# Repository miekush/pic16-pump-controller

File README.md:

# pic16-pump-controller
PIC16 based Pump Controller for Smart Plant Watering and Coffee Makers

# PCB

# License

MKE supports the open source hardware community by sharing hardware design files freely on GitHub!

Please support MKE by purchasing products on [Tindie](https://www.tindie.com/stores/mkengineering/)!

Designed by Mike Kushnerik (miekush)

Licensed under [Creative Commons Attribution-ShareAlike CC BY-SA 4.0](http://creativecommons.org/licenses/by-sa/4.0/)

All text above must be included in any redistribution!

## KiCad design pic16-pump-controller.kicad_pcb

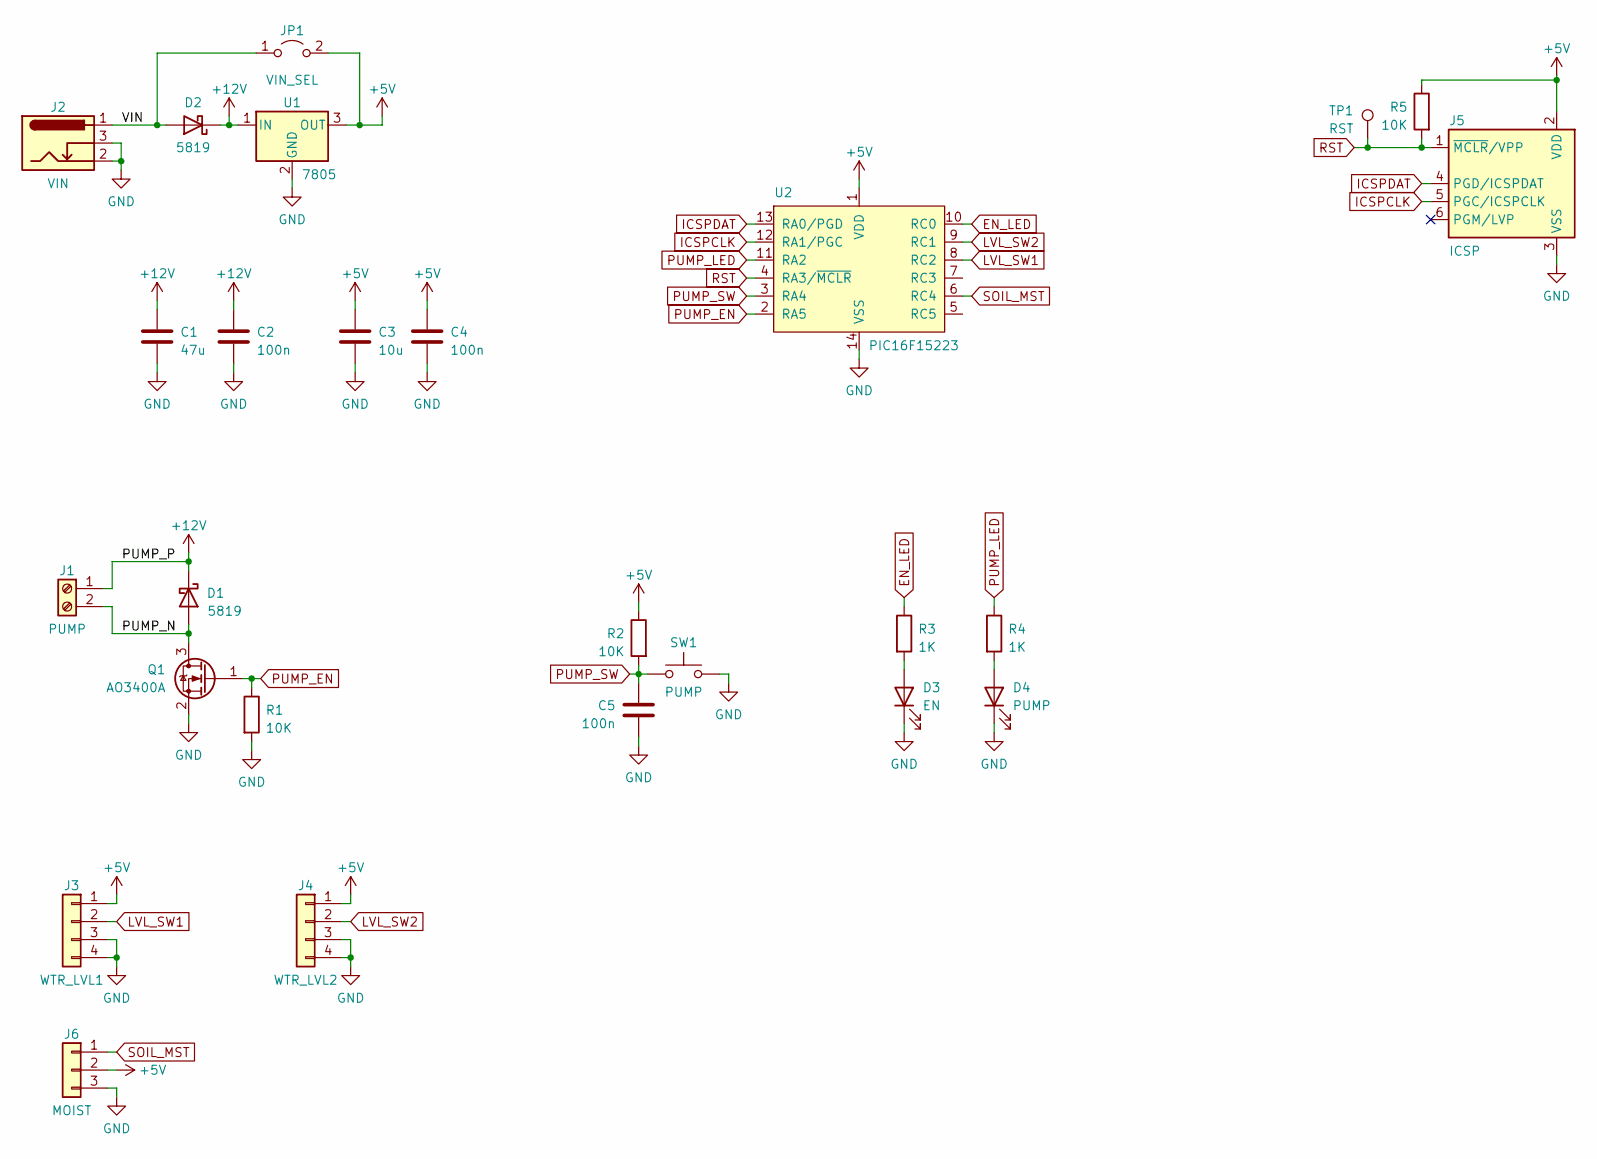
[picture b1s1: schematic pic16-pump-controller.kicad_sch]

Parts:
C1: 47u; CP_Elec_6.3x5.8
C2, C4, C5: 100n; C_0603_1608Metric
C3: 10u; C_0805_2012Metric
D1, D2: 5819; D_SMA
D3: EN; LED_0603_1608Metric
D4: PUMP; LED_0603_1608Metric
J1: PUMP; TerminalBlock_bornier-2_P5.08mm
J2: VIN; BarrelJack_GCT_DCJ200-10-A_Horizontal
J3: WTR_LVL1; PinHeader_1x04_P2.54mm_Vertical
J4: WTR_LVL2; PinHeader_1x04_P2.54mm_Vertical
J5: ICSP; Tag-Connect_TC2030-IDC-NL_2x03_P1.27mm_Vertical
J6: MOIST; PinHeader_1x03_P2.54mm_Vertical
JP1: VIN_SEL; PinHeader_1x02_P2.54mm_Vertical
Q1: AO3400A; SOT-23
R1, R2, R5: 10K; R_0603_1608Metric
R3, R4: 1K; R_0603_1608Metric
SW1: PUMP; SW_Push_1P1T_NO_6x6mm_H9.5mm
TP1: RST; PinHeader_1x01_P2.54mm_Vertical
U1: 7805; SOT-223-3_TabPin2
U2: PIC16F15223; SOIC-14_3.9x8.7mm_P1.27mm

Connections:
+5V: C3.1, C4.1, J3.1, J4.1, J5.2 (VDD), J6.2, JP1.2 (B), R2.1, R5.1, U1.3 (OUT), U2.1 (VDD)
+12V: C1.1, C2.1, D1.1 (K), D2.1 (K), J1.1, U1.1 (IN)
/PUMP_N: D1.2 (A), J1.2, Q1.3 (D)
/VIN: D2.2 (A), J2.1, JP1.1 (A)
EN_LED: R3.1, U2.10 (RC0)
GND: C1.2, C2.2, C3.2, C4.2, C5.2, D3.1 (K), D4.1 (K), J2.2, J2.3, J3.3, J3.4, J4.3, J4.4, J5.3 (VSS), J6.3, Q1.2 (S), R1.2, SW1.2, U1.2 (GND), U2.14 (VSS)
ICSPCLK: J5.5 (PGC/ICSPCLK), U2.12 (RA1/PGC)
ICSPDAT: J5.4 (PGD/ICSPDAT), U2.13 (RA0/PGD)
LVL_SW1: J3.2, U2.8 (RC2)
LVL_SW2: J4.2, U2.9 (RC1)
unnamed: D3.2 (A), R3.2
unnamed: D4.2 (A), R4.2
PUMP_EN: Q1.1 (G), R1.1, U2.2 (RA5)
PUMP_LED: R4.1, U2.11 (RA2)
PUMP_SW: C5.1, R2.2, SW1.1, U2.3 (RA4)
RST: J5.1 (~MCLR/VPP), R5.2, TP1.1, U2.4 (RA3/~MCLR)
SOIL_MST: J6.1, U2.6 (RC4)

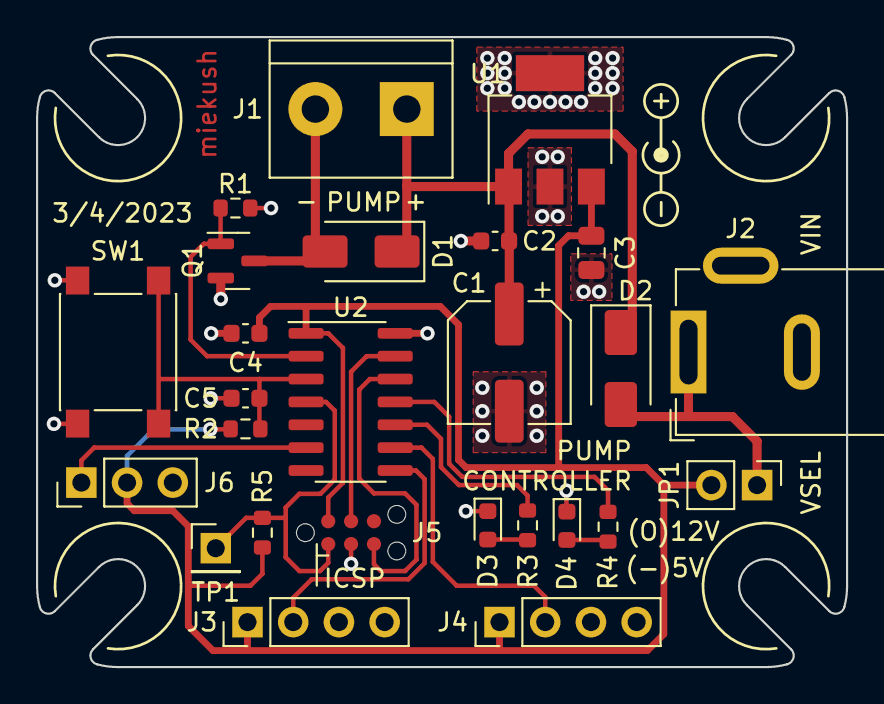
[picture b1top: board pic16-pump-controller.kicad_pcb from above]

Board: 2 copper layers, 45.0 x 35.0 mm, 26 parts (0 on the bottom side), 17 nets.

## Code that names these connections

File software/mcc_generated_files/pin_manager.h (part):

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// get/set PUMP_LED aliases
#define PUMP_LED_TRIS                 TRISAbits.TRISA2
#define PUMP_LED_LAT                  LATAbits.LATA2
#define PUMP_LED_PORT                 PORTAbits.RA2
#define PUMP_LED_WPU                  WPUAbits.WPUA2
#define PUMP_LED_OD                   ODCONAbits.ODCA2
#define PUMP_LED_ANS                  ANSELAbits.ANSA2
#define PUMP_LED_SetHigh()            do { LATAbits.LATA2 = 1; } while(0)
#define PUMP_LED_SetLow()             do { LATAbits.LATA2 = 0; } while(0)
#define PUMP_LED_Toggle()             do { LATAbits.LATA2 = ~LATAbits.LATA2; } while(0)
#define PUMP_LED_GetValue()           PORTAbits.RA2
#define PUMP_LED_SetDigitalInput()    do { TRISAbits.TRISA2 = 1; } while(0)
#define PUMP_LED_SetDigitalOutput()   do { TRISAbits.TRISA2 = 0; } while(0)
#define PUMP_LED_SetPullup()          do { WPUAbits.WPUA2 = 1; } while(0)
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// get/set PUMP_SW aliases
#define PUMP_SW_TRIS                 TRISAbits.TRISA4
#define PUMP_SW_LAT                  LATAbits.LATA4
#define PUMP_SW_PORT                 PORTAbits.RA4
#define PUMP_SW_WPU                  WPUAbits.WPUA4
#define PUMP_SW_OD                   ODCONAbits.ODCA4
#define PUMP_SW_ANS                  ANSELAbits.ANSA4
#define PUMP_SW_SetHigh()            do { LATAbits.LATA4 = 1; } while(0)
#define PUMP_SW_SetLow()             do { LATAbits.LATA4 = 0; } while(0)
#define PUMP_SW_Toggle()             do { LATAbits.LATA4 = ~LATAbits.LATA4; } while(0)
#define PUMP_SW_GetValue()           PORTAbits.RA4
#define PUMP_SW_SetDigitalInput()    do { TRISAbits.TRISA4 = 1; } while(0)
#define PUMP_SW_SetDigitalOutput()   do { TRISAbits.TRISA4 = 0; } while(0)
#define PUMP_SW_SetPullup()          do { WPUAbits.WPUA4 = 1; } while(0)
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// get/set PUMP_EN aliases
#define PUMP_EN_TRIS                 TRISAbits.TRISA5
#define PUMP_EN_LAT                  LATAbits.LATA5
#define PUMP_EN_PORT                 PORTAbits.RA5
#define PUMP_EN_WPU                  WPUAbits.WPUA5
#define PUMP_EN_OD                   ODCONAbits.ODCA5
#define PUMP_EN_ANS                  ANSELAbits.ANSA5
#define PUMP_EN_SetHigh()            do { LATAbits.LATA5 = 1; } while(0)
#define PUMP_EN_SetLow()             do { LATAbits.LATA5 = 0; } while(0)
#define PUMP_EN_Toggle()             do { LATAbits.LATA5 = ~LATAbits.LATA5; } while(0)
#define PUMP_EN_GetValue()           PORTAbits.RA5
#define PUMP_EN_SetDigitalInput()    do { TRISAbits.TRISA5 = 1; } while(0)
#define PUMP_EN_SetDigitalOutput()   do { TRISAbits.TRISA5 = 0; } while(0)
#define PUMP_EN_SetPullup()          do { WPUAbits.WPUA5 = 1; } while(0)
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// get/set STAT_LED aliases
#define STAT_LED_TRIS                 TRISCbits.TRISC0
#define STAT_LED_LAT                  LATCbits.LATC0
#define STAT_LED_PORT                 PORTCbits.RC0
#define STAT_LED_WPU                  WPUCbits.WPUC0
#define STAT_LED_OD                   ODCONCbits.ODCC0
#define STAT_LED_ANS                  ANSELCbits.ANSC0
#define STAT_LED_SetHigh()            do { LATCbits.LATC0 = 1; } while(0)
#define STAT_LED_SetLow()             do { LATCbits.LATC0 = 0; } while(0)
#define STAT_LED_Toggle()             do { LATCbits.LATC0 = ~LATCbits.LATC0; } while(0)
#define STAT_LED_GetValue()           PORTCbits.RC0
#define STAT_LED_SetDigitalInput()    do { TRISCbits.TRISC0 = 1; } while(0)
#define STAT_LED_SetDigitalOutput()   do { TRISCbits.TRISC0 = 0; } while(0)
#define STAT_LED_SetPullup()          do { WPUCbits.WPUC0 = 1; } while(0)
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// get/set LVL_SW2 aliases
#define LVL_SW2_TRIS                 TRISCbits.TRISC1
#define LVL_SW2_LAT                  LATCbits.LATC1
#define LVL_SW2_PORT                 PORTCbits.RC1
#define LVL_SW2_WPU                  WPUCbits.WPUC1
#define LVL_SW2_OD                   ODCONCbits.ODCC1
#define LVL_SW2_ANS                  ANSELCbits.ANSC1
#define LVL_SW2_SetHigh()            do { LATCbits.LATC1 = 1; } while(0)
#define LVL_SW2_SetLow()             do { LATCbits.LATC1 = 0; } while(0)
#define LVL_SW2_Toggle()             do { LATCbits.LATC1 = ~LATCbits.LATC1; } while(0)
#define LVL_SW2_GetValue()           PORTCbits.RC1
#define LVL_SW2_SetDigitalInput()    do { TRISCbits.TRISC1 = 1; } while(0)
#define LVL_SW2_SetDigitalOutput()   do { TRISCbits.TRISC1 = 0; } while(0)
#define LVL_SW2_SetPullup()          do { WPUCbits.WPUC1 = 1; } while(0)
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// get/set LVL_SW1 aliases
#define LVL_SW1_TRIS                 TRISCbits.TRISC2
#define LVL_SW1_LAT                  LATCbits.LATC2
#define LVL_SW1_PORT                 PORTCbits.RC2
#define LVL_SW1_WPU                  WPUCbits.WPUC2
#define LVL_SW1_OD                   ODCONCbits.ODCC2
#define LVL_SW1_ANS                  ANSELCbits.ANSC2
#define LVL_SW1_SetHigh()            do { LATCbits.LATC2 = 1; } while(0)
#define LVL_SW1_SetLow()             do { LATCbits.LATC2 = 0; } while(0)
#define LVL_SW1_Toggle()             do { LATCbits.LATC2 = ~LATCbits.LATC2; } while(0)
#define LVL_SW1_GetValue()           PORTCbits.RC2
#define LVL_SW1_SetDigitalInput()    do { TRISCbits.TRISC2 = 1; } while(0)
#define LVL_SW1_SetDigitalOutput()   do { TRISCbits.TRISC2 = 0; } while(0)
#define LVL_SW1_SetPullup()          do { WPUCbits.WPUC2 = 1; } while(0)
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// get/set MOIST_V aliases
#define MOIST_V_TRIS                 TRISCbits.TRISC4
#define MOIST_V_LAT                  LATCbits.LATC4
#define MOIST_V_PORT                 PORTCbits.RC4
#define MOIST_V_WPU                  WPUCbits.WPUC4
#define MOIST_V_OD                   ODCONCbits.ODCC4
#define MOIST_V_ANS                  ANSELCbits.ANSC4
#define MOIST_V_SetHigh()            do { LATCbits.LATC4 = 1; } while(0)
#define MOIST_V_SetLow()             do { LATCbits.LATC4 = 0; } while(0)
#define MOIST_V_Toggle()             do { LATCbits.LATC4 = ~LATCbits.LATC4; } while(0)
#define MOIST_V_GetValue()           PORTCbits.RC4
#define MOIST_V_SetDigitalInput()    do { TRISCbits.TRISC4 = 1; } while(0)
#define MOIST_V_SetDigitalOutput()   do { TRISCbits.TRISC4 = 0; } while(0)
#define MOIST_V_SetPullup()          do { WPUCbits.WPUC4 = 1; } while(0)
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
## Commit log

2023-03-11 Initial upload

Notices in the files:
software/mcc_generated_files/pin_manager.h:
(c) 2018 Microchip Technology Inc. and its subsidiaries.
